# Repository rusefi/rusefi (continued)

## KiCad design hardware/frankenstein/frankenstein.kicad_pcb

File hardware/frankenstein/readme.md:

This is the older rusEfi board which is not really being developed any more.

See [Frankenso](../frankenso) for the next generation of official rusEfi hardware

See also comparison [Board Comparison](https://rusefi.com/wiki/index.php?title=Hardware:For_Sale)

iBoms are very cool see https://rusefi.com/docs/ibom/frankenstein_latest.html

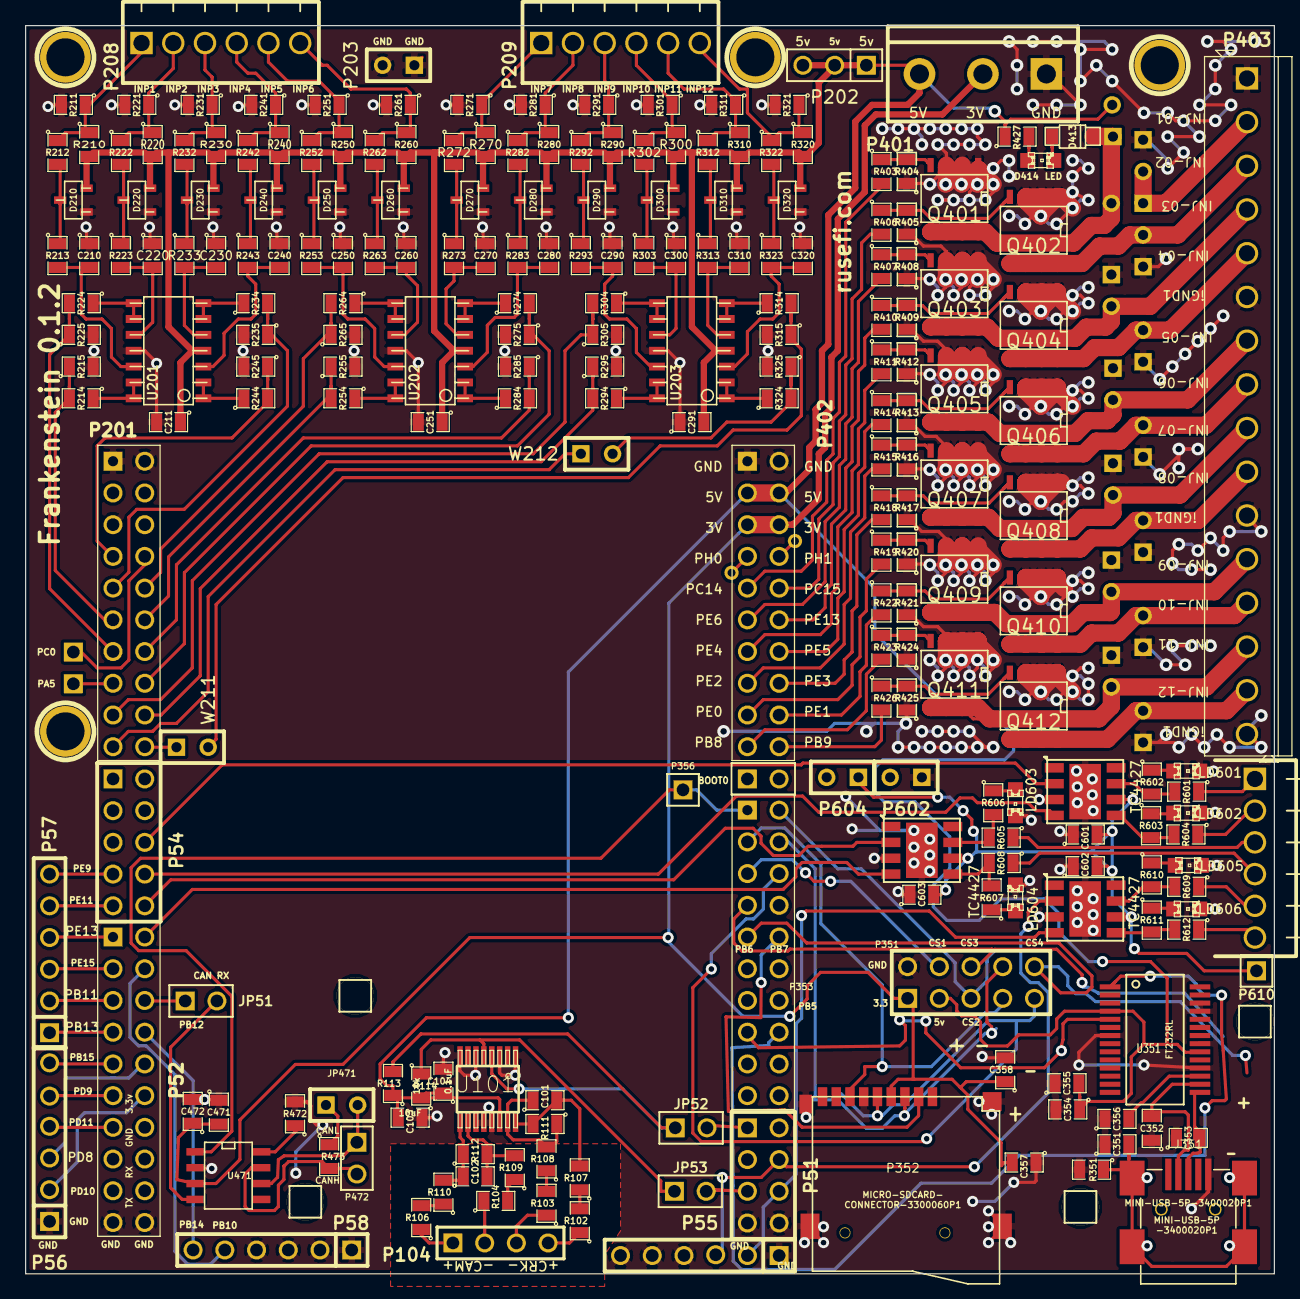
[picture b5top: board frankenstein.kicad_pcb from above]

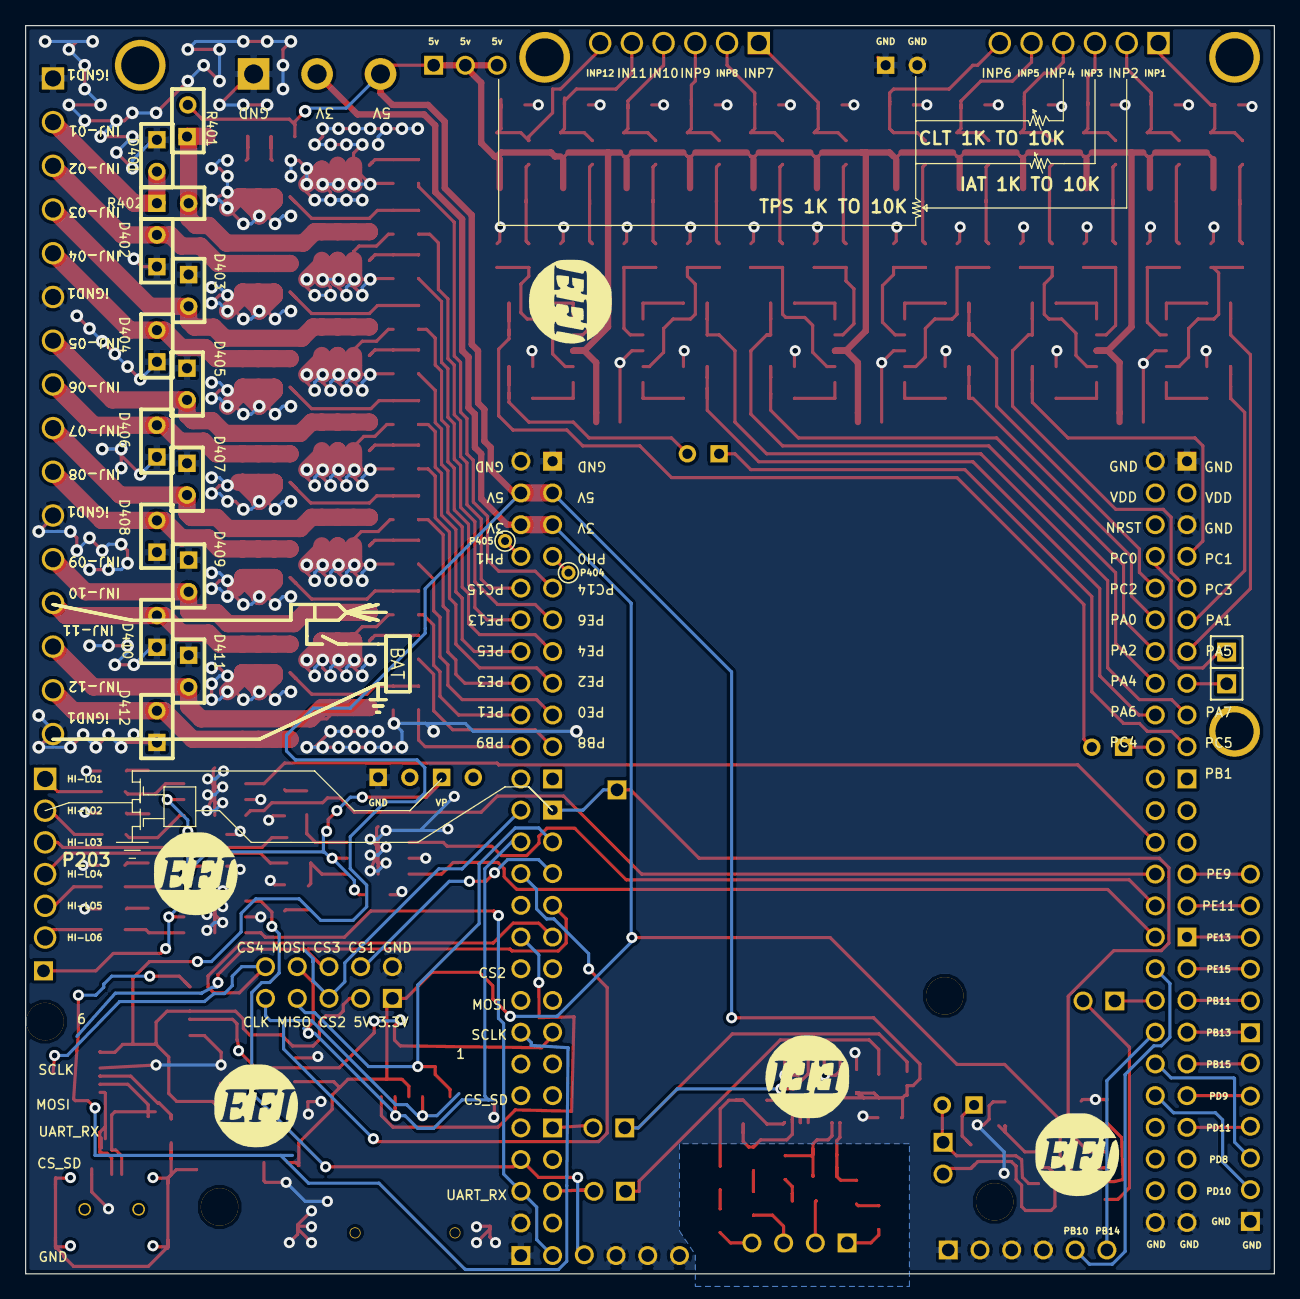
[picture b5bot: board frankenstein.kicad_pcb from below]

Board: 2 copper layers, 100.0 x 99.9 mm, 261 parts (23 on the bottom side), 183 nets.

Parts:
C101, C102: 1000pF; SM0805
C103: 10uF; SM0805
C104, C211, C251, C291, C601, C602, C603: 0.1uF; SM0805
C210, C220, C230, C240, C250, C260, C270, C280, C290, C300, C310, C320: 0.01uF; SM0805
C351: 4700pF; SM0805
C352, C353: 47pF; SM0805
C354, C358, C472: 4.7uF; SM0805
C355, C356, C357, C471: .1uF; SM0805
D210, D220, D230, D240, D250, D260, D270, D280, D290, D300, D310, D320: DOUBLE_SCHOTTKY; sot23
D401, D402, D403, D404, D405, D406, D407, D408, D409, D410, D411, D412: DIODE; SIL-2
D413: DIODE; SOD-123
D414: LED; LED-0805
G101, G201, G305, G471, G601: LOGO; LOGO_F
J351: MINI-USB-5P-3400020P1
JP51, JP52, JP53: JUMPER; PIN_ARRAY_2_A
JP471: JUMPER; SIL-2
LD601, LD602, LD603, LD604, LD605, LD606: LED; LED-0805
M200, M201, M202, M401: CONN_1; 1pin
M351, M352, M470, M471: CONN_1; PIN_ARRAY_1
P51: CONN_4X2; pin_array_4x2
P52, P201: CONN_10X2; PIN_ARRAY_10X2_M
P53: CONN_2; PIN_ARRAY_2X1
P54, P351: CONN_5X2; PIN_ARRAY_5x2
P55, P56, P57, P58: CONN_6; PIN_ARRAY-6X1
P104: CONN_4; PIN_ARRAY_4x1
P202: CONN_3; PIN_ARRAY_3X1
P203, P602, P604: CONN_2; SIL-2
P204, P205, P356, P610: CONN_1; PIN_ARRAY_1
P208, P209: CONN_6; 6_screw_term_.1in
P352: MICRO-SDCARD-CONNECTOR-3300060P1
P353: CONN_10X2; PIN_ARRAY_10X2
P401: CONN_3; bornier3
P402: CONN_10X2; pin_array_10x2
P403: CONN_16; SIL-16_3.5MM
P404, P405: CONN_1; PINTST
P472: CONN_2; PIN_ARRAY_2_A
P603: CONN_6; OSTVN06A150
Q401, Q402, Q403, Q404, Q405, Q406, Q407, Q408, Q409, Q410, Q411, Q412: OVP_DRIVER; SO8E_ST
R102, R103, R104, R106, R107, R108, R109, R110, R111, R112: 5k; SM0805
R113, R114, R212, R222, R232, R242, R252, R262, R272, R282, R292, R302, R312, R322, R472: 10k; SM0805
R210, R220, R230, R240, R250, R260, R270, R280, R290, R300, R310, R320, R602, R603, R606, R607, R610, R611: 2700; SM0805
R211, R221, R231, R241, R251, R261, R271, R281, R291, R301, R311, R321: 500K; SM0805
R213, R223, R233, R243, R253, R263, R273, R283, R293, R303, R313, R323, R601, R604, R605, R608, R609, R612: 100; SM0805
R214, R215, R224, R225, R234, R235, R244, R245, R254, R255, R264, R265, R274, R275, R284, R285, R294, R295, R304, R305, R314, R315, R324, R325: 1500; SM0805
R351: 1M; SM0805
R401: OPT; SIL-2
R402: 0R; SIL-2
R403, R406, R407, R410, R411, R414, R415, R418, R419, R422, R423, R426: 20R; SM0805
R404, R405, R408, R409, R412, R413, R416, R417, R420, R421, R424, R425, R427: 1K; SM0805
R473: 120; SM0805
U101: MAX9926/9927; maxim-10-QSOP16
U201, U202, U203: LMV324IDR; so-14
U351: FT232RL; ssop-28
U471: SN65HVD230; SO8E
U601, U602, U603: TC4427; SOIC8-DFN
W211, W212: TEST; SIL-2

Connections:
/3.3V: C357.2, C358.1, C471.2, C472.1, P351.1, P352.4, P401.2, P402.5, P402.6, U471.3
/5V: C103.2, C104.1, C211.1, C251.1, C291.2, C354.1, C355.2, D210.3, D220.3, D230.3, D240.3, D250.3, D260.3, D270.3, D280.3, D290.3, D300.3, D310.3, D320.3, P202.1, P202.2, P202.3, P351.3, P401.3, P402.3, P402.4, R113.1, R114.2, R210.2, R220.2, R230.2, R240.2, R250.2, R260.2, R270.2, R280.2, R290.2, R300.2, R310.2, R320.2, R401.2, R427.1, U101.14, U201.4, U202.4, U203.4, U351.4, U351.20
/CAM: JP53.1, R114.1, U101.5
/CAM+: P104.1, R106.1
/CAM-: P104.2, R104.1
/CANH: P472.2, R473.2, U471.7
/CANL: JP471.2, P472.1, U471.6
/CAN_RX: JP51.2, U471.4
/CAN_TX: P353.1, P356.1, U471.1
/CRANK: JP52.1, R113.2, U101.4
/CRK2+: P104.4, R102.1
/CRK2-: P104.3, R103.1
/CS1: P351.4, P353.5
/CS2: P351.5, P353.2
/CS3: P351.6, P353.7
/CS4: P351.10, P353.9
/CS_SD_MODULE: P352.2, P353.10
/HL1: P603.1, R601.1
/HL2: P603.2, R604.1
/HL3: P603.3, R605.1
/HL4: P603.4, R608.1
/HL5: P603.5, R609.1
/HL6: P603.6, R612.1
/H_IN1: P54.8, U601.4
/H_IN2: P54.10, U602.2
/H_IN3: P54.6, U601.2
/H_IN4: P52.2, U602.4
/H_IN5: P51.6, P55.2, U603.4
/H_IN6: P51.4, P55.3, U603.2
/INJ-01: D413.2, Q401.2, R401.1, R402.2
/INJ-01_2: D401.2, P403.2, R402.1
/INJ-01_5V: P402.9, R403.2
/INJ-02: D402.2, P403.3, Q402.2
/INJ-02_5V: P402.10, R406.2
/INJ-03: D403.2, P403.4, Q403.2
/INJ-03_5V: P402.11, R407.2
/INJ-04: D404.2, P403.5, Q404.2
/INJ-04_5V: P402.12, R410.2
/INJ-05: D405.2, P403.7, Q405.2
/INJ-05_5V: P402.13, R411.2
/INJ-06: D406.2, P403.8, Q406.2
/INJ-06_5V: P402.14, R414.2
/INJ-07: D407.2, P403.9, Q407.2
/INJ-07_5V: P402.15, R415.2
/INJ-08: D408.2, P403.10, Q408.2
/INJ-08_5V: P402.16, R418.2
/INJ-09: D409.2, P403.12, Q409.2
/INJ-09_5V: P402.17, R419.2
/INJ-10: D410.2, P403.13, Q410.2
/INJ-10_5V: P402.18, R422.2
/INJ-11: D411.2, P403.14, Q411.2
/INJ-11_5V: P402.19, R423.2
/INJ-12: D412.2, P403.15, Q412.2
/INJ-12_5V: P402.20, R426.2
/INP1: P208.1, R210.1, R211.1, R212.1
/INP2: P208.2, R220.1, R221.1, R222.1
/INP3: P208.3, R230.1, R231.1, R232.1
/INP4: P208.4, R240.1, R241.1, R242.1
/INP5: P208.5, R250.1, R251.1, R252.1
/INP6: P208.6, R260.1, R261.1, R262.1
/INP7: P209.1, R270.1, R271.1, R272.1
/INP8: P209.2, R280.1, R281.1, R282.1
/INP9: P209.3, R290.1, R291.1, R292.1
/INP10: P209.4, R300.1, R301.1, R302.1
/INP11: P209.5, R310.1, R311.1, R312.1
/INP12: P209.6, R320.1, R321.1, R322.1
/OUT1: P201.11, R214.2, R215.1
/OUT2: P201.13, R224.2, R225.1
/OUT3: P201.9, R234.2, R235.1
/OUT4: P201.7, R244.2, R245.1
/OUT5: P201.12, R254.2, R255.1
/OUT6: P201.10, R264.2, R265.1
/OUT7: P201.16, R274.2, R275.1
/OUT8: P201.14, R284.2, R285.1
/OUT9: P201.18, R294.2, R295.1
/OUT10: P201.17, R304.2, R305.1
/OUT11: P201.20, W211.1
/OUT12: P201.19, W212.1
/PA5: P201.15, P204.1
/PA8: JP52.2, P51.1
/PB10: P52.4, P58.5
/PB11: P52.5, P57.2
/PB12: JP51.1, P52.6
/PB13: P52.7, P57.1
/PB14: P52.8, P58.6
/PB15: P52.9, P56.6
/PC0: P201.8, P205.1
/PC6: JP53.2, P51.5
/PD8: P52.10, P56.3
/PD9: P52.11, P56.5
/PD10: P52.12, P56.2
/PD11: P52.13, P56.4
/PE9: P54.7, P57.6
/PE11: P54.9, P57.5
/PE13: P52.1, P57.4
/PE15: P52.3, P57.3
/PH0: P402.7, P404.1
/PH1: P402.8, P405.1
/SPI_MISO: P351.7, P352.7, P353.3
/SPI_MOSI: P351.8, P352.3, P353.4
/SPI_SCK: P351.9, P352.5, P353.6
/USART_RX: P353.15, U351.5
/USART_TX: P353.16, U351.1
/VP: C601.2, C602.2, C603.2, P604.1, P610.1, U601.6, U602.6, U603.6
F-000020: R102.2, R107.1
F-000021: R104.2, R109.1
F-000023: R106.2, R110.1
F-000024: R103.2, R108.1
F-000025: C101.1, R108.2, R111.1, U101.15
F-000026: C101.2, R107.2, R111.2, U101.16
F-000027: C102.1, R110.2, R112.1, U101.9
F-000028: C102.2, R109.2, R112.2, U101.10
F-000056: D280.2, R282.2, R283.1
F-000057: R214.1, U201.13, U201.14
F-000058: R224.1, U201.8, U201.9
F-000059: D270.2, R272.2, R273.1
F-000060: R244.1, U201.1, U201.2
F-000061: D300.2, R302.2, R303.1
F-000062: D290.2, R292.2, R293.1
F-000063: R304.1, U203.8, U203.9
F-000064: R294.1, U203.13, U203.14
F-000065: C290.2, R293.2, U203.12
F-000066: D250.2, R252.2, R253.1
F-000067: C300.2, R303.2, U203.10
F-000068: R314.1, U203.6, U203.7
F-000069: R324.1, U203.1, U203.2
F-000070: C310.2, R313.2, U203.5
F-000071: C320.2, R323.2, U203.3
F-000072: D320.2, R322.2, R323.1
F-000073: D260.2, R262.2, R263.1
F-000074: D310.2, R312.2, R313.1
F-000075: R324.2, R325.1, W212.2
F-000076: R314.2, R315.1, W211.2
F-000077: C250.2, R253.2, U202.12
F-000078: D210.2, R212.2, R213.1
F-000079: R254.1, U202.13, U202.14
F-000080: R274.1, U202.6, U202.7
F-000081: R264.1, U202.8, U202.9
F-000082: C240.2, R243.2, U201.3
F-000083: C230.2, R233.2, U201.5
F-000084: C270.2, R273.2, U202.5
F-000085: C280.2, R283.2, U202.3
F-000086: C220.2, R223.2, U201.10
F-000087: D220.2, R222.2, R223.1
F-000088: C210.2, R213.2, U201.12
F-000089: C260.2, R263.2, U202.10
F-000090: R284.1, U202.1, U202.2
F-000091: D240.2, R242.2, R243.1
F-000093: D230.2, R232.2, R233.1
F-000094: R234.1, U201.6, U201.7
F-0000108: C353.2, J351.3, U351.15
F-0000110: C351.2, J351.6, R351.1
F-0000112: C356.2, U351.17
F-0000115: C352.2, J351.4, U351.16
F-0000143: Q408.1, R417.2, R418.1
F-0000144: Q404.1, R409.2, R410.1
F-0000145: Q406.1, R413.2, R414.1
F-0000146: Q402.1, R405.2, R406.1
F-0000147: D414.1, R427.2
F-0000148: Q410.1, R421.2, R422.1
F-0000149: D413.1, D414.2
F-0000150: Q412.1, R425.2, R426.1
F-0000151: Q401.1, R403.1, R404.2
F-0000152: Q405.1, R411.1, R412.2
F-0000153: Q403.1, R407.1, R408.2
F-0000154: Q409.1, R419.1, R420.2
F-0000155: Q407.1, R415.1, R416.2
F-0000156: Q411.1, R423.1, R424.2
F-0000161: JP471.1, R473.1
F-0000162: R472.1, U471.8
GND: C103.1, C104.2, C210.1, C211.2, C220.1, C230.1, C240.1, C250.1, C251.2, C260.1, C270.1, C280.1, C290.1, C291.1, C300.1, C310.1, C320.1, C351.1, C352.1, C353.1, C354.2, C355.1, C356.1, C357.1, C358.2, C471.1, C472.2, C601.1, C602.1, C603.1, D210.1, D220.1, D230.1, D240.1, D250.1, D260.1, D270.1, D280.1, D290.1, D300.1, D310.1, D320.1, D401.1, D402.1, D403.1, D404.1, D405.1, D406.1, D407.1, D408.1, D409.1, D410.1, D411.1, D412.1, J351.1, LD601.2, LD602.2, LD603.2, LD604.2, LD605.2, LD606.2, P51.7, P51.8, P52.19, P52.20, P55.1, P55.4, P55.5, P55.6, P56.1, P58.1, P58.2, P58.3, P58.4, P201.1, P201.2, P201.5, P203.1, P203.2, P351.2, P352.6, P352.G1, P352.G2, P352.G3, P352.G4, P401.1, P402.1, P402.2, P403.1, P403.6, P403.11, P403.16, P602.1, Q401.3, Q402.3, Q403.3, Q404.3, Q405.3, Q406.3, Q407.3, Q408.3, Q409.3, Q410.3, Q411.3, Q412.3, R211.2, R215.2, R221.2, R225.2, R231.2, R235.2, R241.2, R245.2, R251.2, R255.2, R261.2, R265.2, R271.2, R275.2, R281.2, R285.2, R291.2, R295.2, R301.2, R305.2, R311.2, R315.2, R321.2, R325.2, R351.2, R404.1, R405.1, R408.1, R409.1, R412.1, R413.1, R416.1, R417.1, R420.1, R421.1, R424.1, R425.1, R472.2, U101.1, U101.3, U101.6, U101.8, U101.11, U101.12, U101.13, U201.11, U202.11, U203.11, U351.7, U351.18, U351.21, U351.25, U351.26, U471.2, U601.3, U601.9, U602.3, U602.9, U603.3, U603.9
unnamed: LD604.1, R607.1
unnamed: LD602.1, R603.1
unnamed: LD605.1, R610.1
unnamed: LD603.1, R606.1
unnamed: LD601.1, R602.1
unnamed: R609.2, R610.2, U603.7
unnamed: R603.2, R604.2, U601.5
unnamed: R601.2, R602.2, U601.7
unnamed: R607.2, R608.2, U602.5
unnamed: R605.2, R606.2, U602.7
unnamed: LD606.1, R611.1
unnamed: R611.2, R612.2, U603.5

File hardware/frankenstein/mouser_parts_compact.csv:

### this file was generated by rusEfi bom_builder on Sat Mar 08 11:58:11 CST 2014
### 292 components in 2047 lines of frankenstein.cmp
### 65 kinds of components in input file
### 5 entries in BOM dictionary bom_dictionary_mouser.csv
### 0 entries in ignore list
### no BOM record for 1pin_CONN_1
### no BOM record for LED-0805_GREEN
### no BOM record for LED-0805_LED
### no BOM record for LED-0805_RED
### no BOM record for LED-1206_LED
### no BOM record for LOGO_F_LOGO
### no BOM record for LOGO_LOGO
### no BOM record for MICRO-SDCARD-CONNECTOR-3300060P1_MICRO-SDCARD-CONNECTOR-3300060P1
### no BOM record for OSTVN06A150_CONN_6
### no BOM record for PIN_ARRAY-6X1_CONN_6
### no BOM record for PIN_ARRAY_10X2_CONN_10X2
### no BOM record for PIN_ARRAY_10X2_M_CONN_10X2
### no BOM record for PIN_ARRAY_1_CONN_1
### no BOM record for PIN_ARRAY_2X1_CONN_2
### no BOM record for PIN_ARRAY_2_A_CONN_2
### no BOM record for PIN_ARRAY_2_A_JUMPER
### no BOM record for PIN_ARRAY_3X1_CONN_3
### no BOM record for PIN_ARRAY_3_A_CONN_3
### no BOM record for PIN_ARRAY_4x1_CONN_4
### no BOM record for PIN_ARRAY_5x2_CONN_5X2
### no BOM record for SIL-16_3.5MM_CONN_16
### no BOM record for SIL-2_0R
### no BOM record for SIL-2_CONN_2
### no BOM record for SIL-2_DIODE
### no BOM record for SIL-2_JUMPER
### no BOM record for SIL-2_OPT
### no BOM record for SIL-2_TEST
### no BOM record for SM0805_.1uF
### no BOM record for SM0805_0.01uF
### no BOM record for SM0805_0.1uF
### no BOM record for SM0805_100
### no BOM record for SM0805_1000pF
### no BOM record for SM0805_10K
### no BOM record for SM0805_10k
### no BOM record for SM0805_10uF
### no BOM record for SM0805_120
### no BOM record for SM0805_1500
### no BOM record for SM0805_1K
### no BOM record for SM0805_1M
### no BOM record for SM0805_1k
### no BOM record for SM0805_1uF
### no BOM record for SM0805_20K
### no BOM record for SM0805_20R
### no BOM record for SM0805_2700
### no BOM record for SM0805_4.7uF
### no BOM record for SM0805_4700pF
### no BOM record for SM0805_47pF
### no BOM record for SM0805_500K
### no BOM record for SM0805_5k
### no BOM record for SM0805_LED
### no BOM record for SM1206_LED
### no BOM record for SO8E_ST_OVP_DRIVER
### no BOM record for SOD-123_DIODE
### no BOM record for bornier3_CONN_3
### no BOM record for msoic-8_TC4427AVOA
### no BOM record for pin_array_10x2_CONN_10X2
### no BOM record for pin_array_3x2_CONN_3X2
### no BOM record for pin_array_4x2_CONN_4X2
### no BOM record for sot23_DOUBLE_SCHOTTKY
### no BOM record for uMAX-uSOP_10_MAX9939




1,656-DX2R005HN2E700,mini USB socket
1,296-11654-1-ND,CAN driver
1,700-MAX9926UAEE,VR chip
3,595-LMV324IDR,quad op-amp
1,895-FT232RL,USB TTL chip
